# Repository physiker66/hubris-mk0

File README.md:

# hubris-mk0
homebrew computer based on 74xx chips

This work is based in large parts on Ben Eaters tutorial (see: https://eater.net). Ben's contributions are greatly appreciated.

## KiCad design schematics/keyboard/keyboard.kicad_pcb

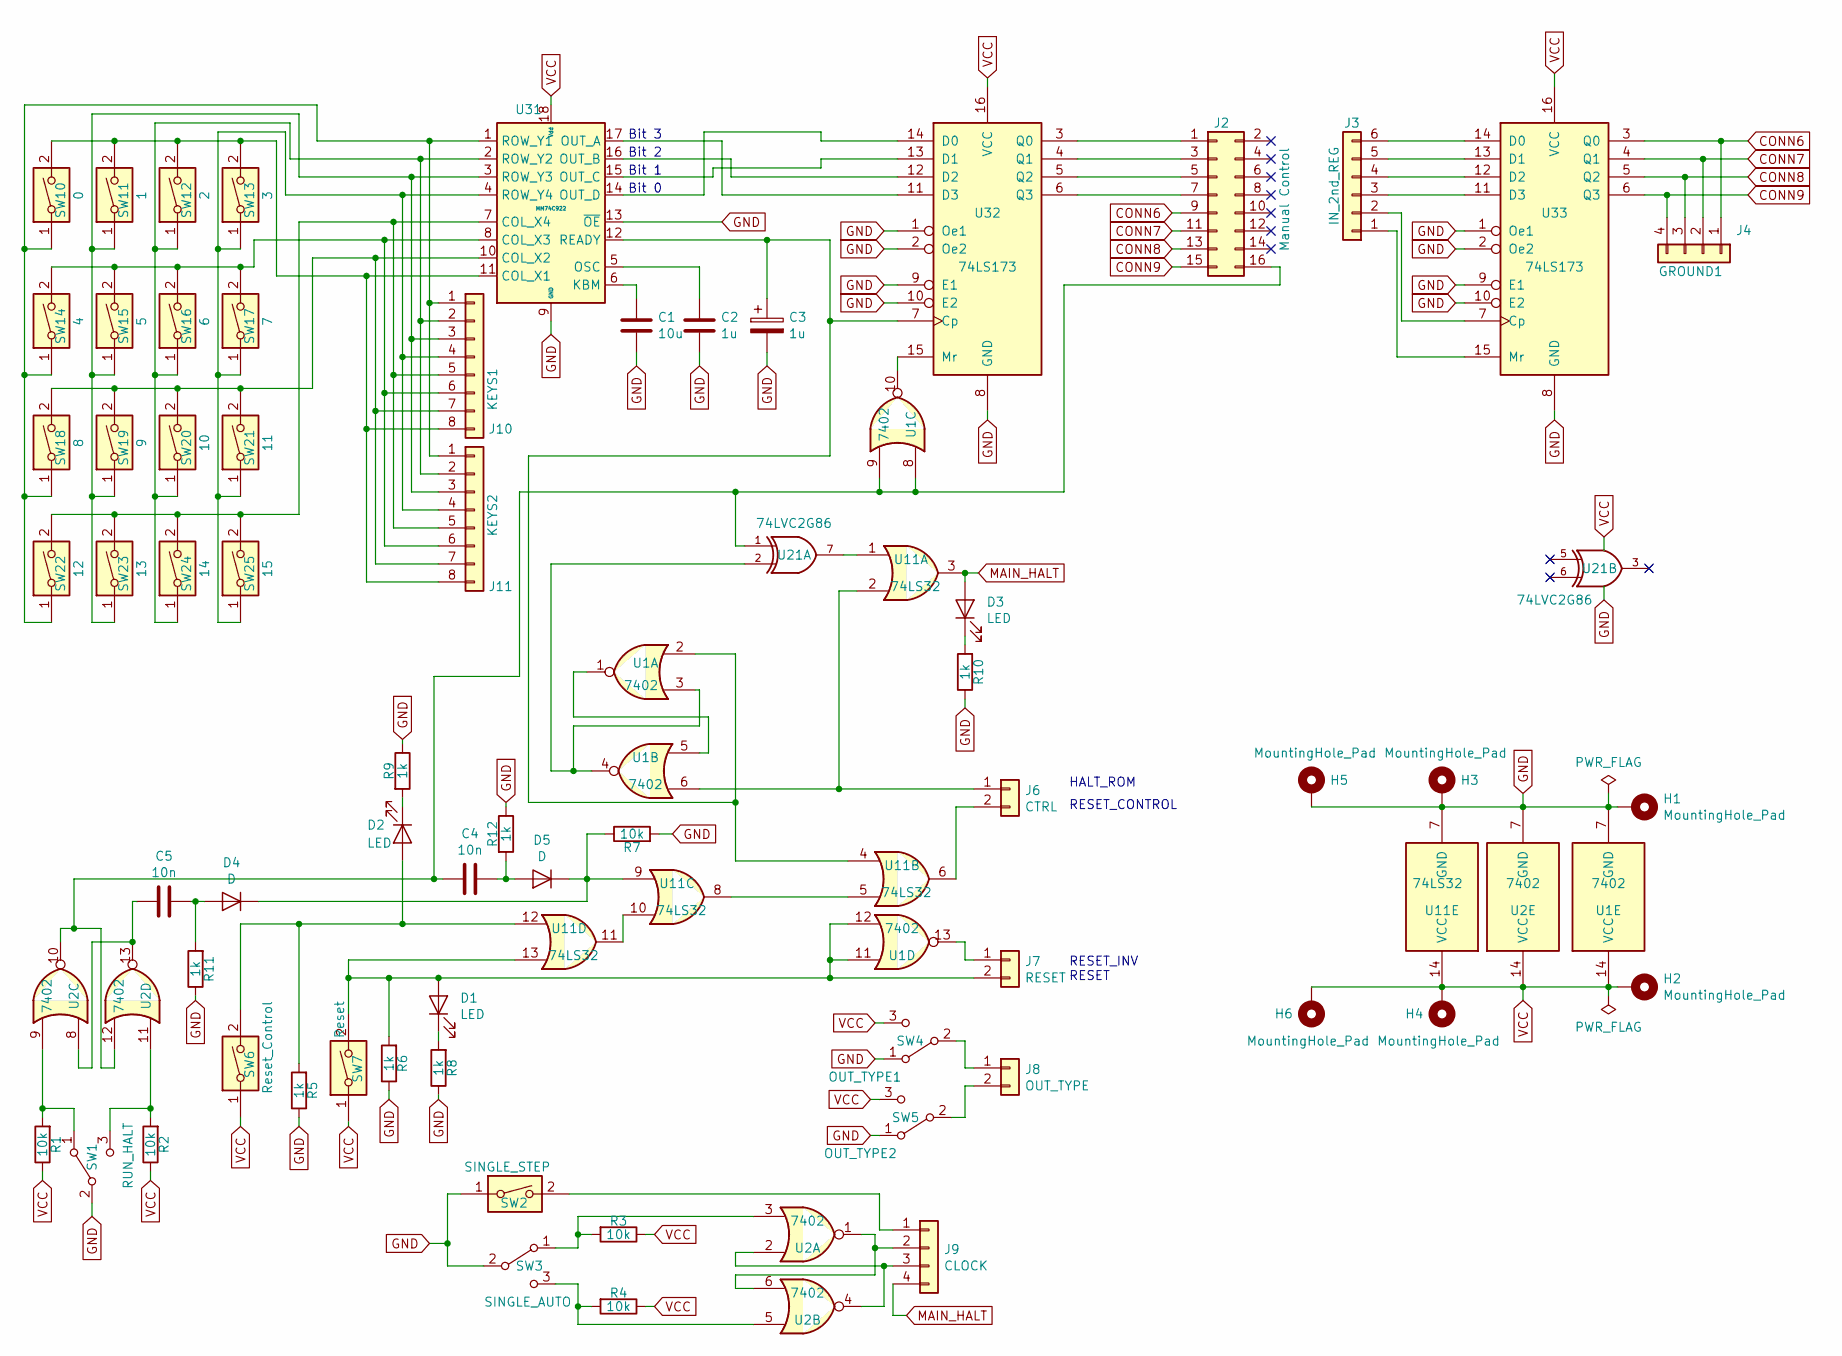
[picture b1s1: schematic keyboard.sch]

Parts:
C1: 10u; CP_Radial_D5.0mm_P2.50mm
C2: 1u; CP_Radial_D5.0mm_P2.50mm
C3: 1u; CP_Radial_D6.3mm_P2.50mm
C4, C5: 10n; C_Disc_D5.0mm_W2.5mm_P2.50mm
D1, D2, D3: LED; LED_D5.0mm
D4, D5: D; D_A-405_P7.62mm_Horizontal
H1, H2, H3, H4, H5, H6: MountingHole_Pad; MountingHole_3.5mm_Pad_Via
J2: Manual Control; PinHeader_2x08_P2.54mm_Vertical
J3: IN_2nd_REG; PinHeader_1x06_P2.54mm_Vertical
J4: GROUND1; PinHeader_1x04_P2.54mm_Vertical
J6: CTRL; PinHeader_1x02_P2.54mm_Vertical
J7: RESET; PinHeader_1x02_P2.54mm_Vertical
J8: OUT_TYPE; PinHeader_1x02_P2.54mm_Vertical
J9: CLOCK; PinHeader_1x04_P2.54mm_Vertical
J10: KEYS1; PinHeader_1x08_P2.54mm_Vertical
J11: KEYS2; PinHeader_1x08_P2.54mm_Vertical
R1, R2, R3, R4, R7: 10k; R_Axial_DIN0207_L6.3mm_D2.5mm_P7.62mm_Horizontal
R5, R6, R8, R9, R10, R11, R12: 1k; R_Axial_DIN0207_L6.3mm_D2.5mm_P7.62mm_Horizontal
SW1: RUN_HALT; SW_SPDT_1P2T
SW2: SINGLE_STEP; SW_PUSH-12mm
SW3: SINGLE_AUTO; SW_SPDT_1P2T
SW4: OUT_TYPE1; SW_Slide_1P2T
SW5: OUT_TYPE2; SW_Slide_1P2T
SW6: Reset_Control; SW_PUSH-12mm
SW7: Reset; SW_PUSH-12mm
SW10: 0; SW_PUSH-12mm
SW11: 1; SW_PUSH-12mm
SW12: 2; SW_PUSH-12mm
SW13: 3; SW_PUSH-12mm
SW14: 4; SW_PUSH-12mm
SW15: 5; SW_PUSH-12mm
SW16: 6; SW_PUSH-12mm
SW17: 7; SW_PUSH-12mm
SW18: 8; SW_PUSH-12mm
SW19: 9; SW_PUSH-12mm
SW20: 10; SW_PUSH-12mm
SW21: 11; SW_PUSH-12mm
SW22: 12; SW_PUSH-12mm
SW23: 13; SW_PUSH-12mm
SW24: 14; SW_PUSH-12mm
SW25: 15; SW_PUSH-12mm
U1, U2: 7402; DIP-14_W7.62mm
U11: 74LS32; DIP-14_W7.62mm
U21: 74LVC2G86; DIP-8_W7.62mm
U31: MM74C922; DIP-18_W7.62mm
U32, U33: 74LS173; DIP-16_W7.62mm

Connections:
CONN6: J2.9, J4.1, U33.3 (Q0)
CONN7: J2.11, J4.2, U33.4 (Q1)
CONN8: J2.13, J4.3, U33.5 (Q2)
CONN9: J2.15, J4.4, U33.6 (Q3)
GND: C1.2, C2.2, C3.2, H1.1, H3.1, H5.1, R5.1, R6.1, R7.2, R8.1, R9.1, R10.1, R11.1, R12.1, SW1.2 (B), SW2.1, SW3.2 (B), SW4.1 (A), SW5.1 (A), U1.7 (GND), U2.7 (GND), U11.7 (GND), U21.4 (GND), U31.9 (GND), U31.13 (~OE~), U32.1 (Oe1), U32.2 (Oe2), U32.8 (GND), U32.9 (E1), U32.10 (E2), U33.1 (Oe1), U33.2 (Oe2), U33.8 (GND), U33.9 (E1), U33.10 (E2)
MAIN_HALT: D3.2 (A), J9.4, U11.3
unnamed: C1.1, U31.6 (KBM)
unnamed: C2.1, U31.5 (OSC)
unnamed: C3.1, U1.2, U11.4, U31.12 (READY), U32.7 (Cp)
unnamed: C4.1, D5.2 (A), R12.2
unnamed: C4.2, J2.16, U1.8, U1.9, U2.10, U2.12, U21.1
unnamed: C5.1, D4.2 (A), R11.2
unnamed: C5.2, U2.8, U2.13
unnamed: D1.1 (K), R8.2
unnamed: D1.2 (A), J7.2, R6.2, SW7.2, U1.11, U1.12, U11.13
unnamed: D2.1 (K), R9.2
unnamed: D2.2 (A), R5.2, SW6.2, U11.12
unnamed: D3.1 (K), R10.2
unnamed: D4.1 (K), D5.1 (K), R7.1, U11.9
unnamed: J2.1, U32.3 (Q0)
unnamed: J2.3, U32.4 (Q1)
unnamed: J2.5, U32.5 (Q2)
unnamed: J2.7, U32.6 (Q3)
unnamed: J3.1, U33.15 (Mr)
unnamed: J3.2, U33.7 (Cp)
unnamed: J3.3, U33.11 (D3)
unnamed: J3.4, U33.12 (D2)
unnamed: J3.5, U33.13 (D1)
unnamed: J3.6, U33.14 (D0)
unnamed: J6.1, U1.6, U11.2
unnamed: J6.2, U11.6
unnamed: J7.1, U1.13
unnamed: J8.1, SW4.2 (B)
unnamed: J8.2, SW5.2 (B)
unnamed: J9.1, SW2.2
unnamed: J9.2, U2.1, U2.6
unnamed: J9.3, U2.2, U2.4
unnamed: J10.1, J11.1, SW10.1, SW14.1, SW18.1, SW22.1, U31.1 (ROW_Y1)
unnamed: J10.2, J11.2, SW12.1, SW16.1, SW20.1, SW24.1, U31.2 (ROW_Y2)
unnamed: J10.3, J11.3, SW11.1, SW15.1, SW19.1, SW23.1, U31.3 (ROW_Y3)
unnamed: J10.4, J11.4, SW13.1, SW17.1, SW21.1, SW25.1, U31.4 (ROW_Y4)
unnamed: J10.5, J11.5, SW22.2, SW23.2, SW24.2, SW25.2, U31.7 (COL_X4)
unnamed: J10.6, J11.6, SW14.2, SW15.2, SW16.2, SW17.2, U31.8 (COL_X3)
unnamed: J10.7, J11.7, SW18.2, SW19.2, SW20.2, SW21.2, U31.10 (COL_X2)
unnamed: J10.8, J11.8, SW10.2, SW11.2, SW12.2, SW13.2, U31.11 (COL_X1)
unnamed: R1.2, SW1.1 (A), U2.9
unnamed: R2.2, SW1.3 (C), U2.11
unnamed: R3.2, SW3.1 (A), U2.3
unnamed: R4.2, SW3.3 (C), U2.5
unnamed: U1.1, U1.5
unnamed: U1.3, U1.4, U21.2
unnamed: U1.10, U32.15 (Mr)
unnamed: U11.1, U21.7
unnamed: U11.5, U11.8
unnamed: U11.10, U11.11
unnamed: U31.14 (OUT_D), U32.14 (D0)
unnamed: U31.15 (OUT_C), U32.13 (D1)
unnamed: U31.16 (OUT_B), U32.12 (D2)
unnamed: U31.17 (OUT_A), U32.11 (D3)
VCC: H2.1, H4.1, H6.1, R1.1, R2.1, R3.1, R4.1, SW4.3 (C), SW5.3 (C), SW6.1, SW7.1, U1.14 (VCC), U2.14 (VCC), U11.14 (VCC), U21.8 (VCC), U31.18 (Vdd), U32.16 (VCC), U33.16 (VCC)

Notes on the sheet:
RESET_INV RESET
HALT_ROM
RESET_CONTROL
Bit 0
Bit 1
Bit 2
Bit 3

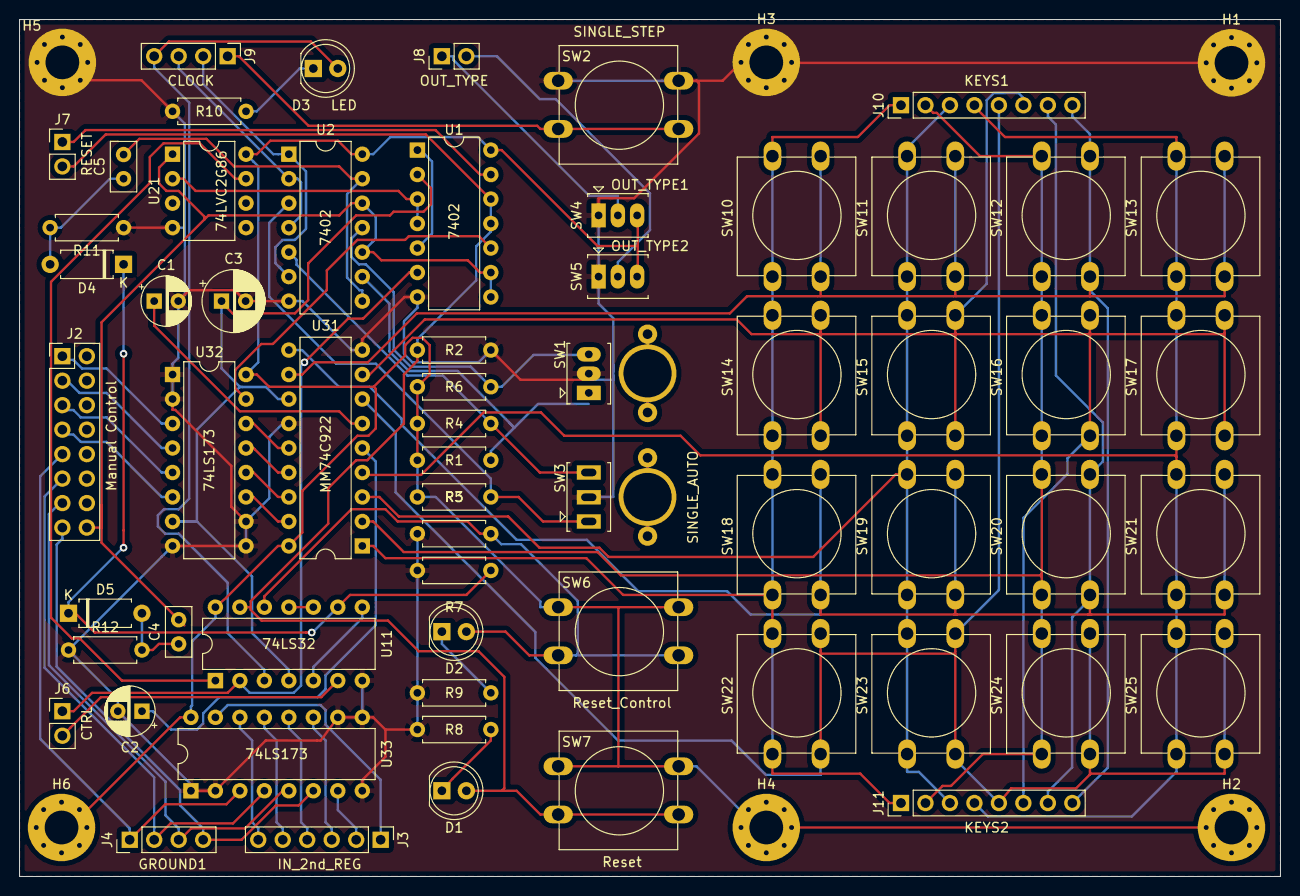
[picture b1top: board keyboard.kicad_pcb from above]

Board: 2 copper layers, 130.8 x 88.9 mm, 67 parts (0 on the bottom side), 60 nets.

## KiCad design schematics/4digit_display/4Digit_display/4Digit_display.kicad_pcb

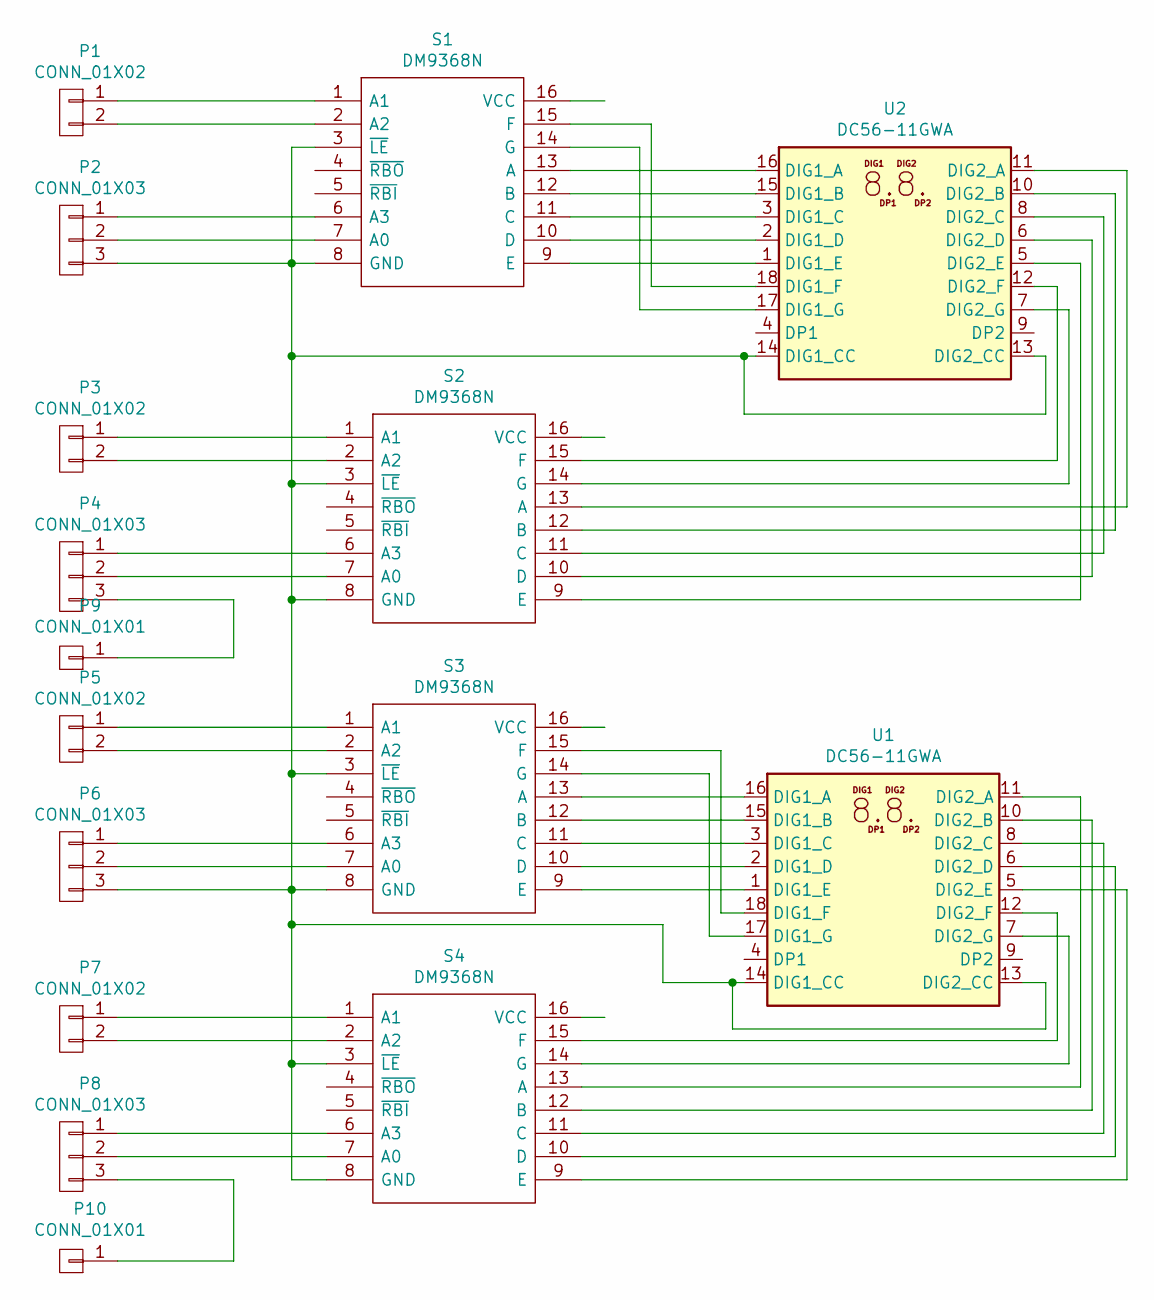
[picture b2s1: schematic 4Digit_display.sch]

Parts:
P1: CONN_01X02; PinSocket_1x02_P2.54mm_Vertical
P2, P4, P6, P8: CONN_01X03; PinHeader_1x03_P2.54mm_Vertical
P3, P5, P7: CONN_01X02; PinHeader_1x02_P2.54mm_Vertical
P9, P10: CONN_01X01; PinHeader_1x01_P2.54mm_Vertical
S1, S2, S3, S4: DM9368N; DIP-16_W7.62mm; Manufacturer_Part_Number DM9368N; Mouser Part Number 512-DM9368N
U1, U2: DC56-11GWA; DA56-11CGKWA

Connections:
unnamed: P1.1, S1.1 (A1)
unnamed: P1.2, S1.2 (A2)
unnamed: P2.1, S1.6 (A3)
unnamed: P2.2, S1.7 (A0)
unnamed: P2.3, P6.3, S1.3 (~LE), S1.8 (GND), S2.3 (~LE), S2.8 (GND), S3.3 (~LE), S3.8 (GND), S4.3 (~LE), S4.8 (GND), U1.13 (DIG2_CC), U1.14 (DIG1_CC), U2.13 (DIG2_CC), U2.14 (DIG1_CC)
unnamed: P3.1, S2.1 (A1)
unnamed: P3.2, S2.2 (A2)
unnamed: P4.1, S2.6 (A3)
unnamed: P4.2, S2.7 (A0)
unnamed: P4.3, P9.1
unnamed: P5.1, S3.1 (A1)
unnamed: P5.2, S3.2 (A2)
unnamed: P6.1, S3.6 (A3)
unnamed: P6.2, S3.7 (A0)
unnamed: P7.1, S4.1 (A1)
unnamed: P7.2, S4.2 (A2)
unnamed: P8.1, S4.6 (A3)
unnamed: P8.2, S4.7 (A0)
unnamed: P8.3, P10.1
unnamed: S1.9 (E), U2.1 (DIG1_E)
unnamed: S1.10 (D), U2.2 (DIG1_D)
unnamed: S1.11 (C), U2.3 (DIG1_C)
unnamed: S1.12 (B), U2.15 (DIG1_B)
unnamed: S1.13 (A), U2.16 (DIG1_A)
unnamed: S1.14 (G), U2.17 (DIG1_G)
unnamed: S1.15 (F), U2.18 (DIG1_F)
unnamed: S2.9 (E), U2.5 (DIG2_E)
unnamed: S2.10 (D), U2.6 (DIG2_D)
unnamed: S2.11 (C), U2.8 (DIG2_C)
unnamed: S2.12 (B), U2.10 (DIG2_B)
unnamed: S2.13 (A), U2.11 (DIG2_A)
unnamed: S2.14 (G), U2.7 (DIG2_G)
unnamed: S2.15 (F), U2.12 (DIG2_F)
unnamed: S3.9 (E), U1.1 (DIG1_E)
unnamed: S3.10 (D), U1.2 (DIG1_D)
unnamed: S3.11 (C), U1.3 (DIG1_C)
unnamed: S3.12 (B), U1.15 (DIG1_B)
unnamed: S3.13 (A), U1.16 (DIG1_A)
unnamed: S3.14 (G), U1.17 (DIG1_G)
unnamed: S3.15 (F), U1.18 (DIG1_F)
unnamed: S4.9 (E), U1.5 (DIG2_E)
unnamed: S4.10 (D), U1.6 (DIG2_D)
unnamed: S4.11 (C), U1.8 (DIG2_C)
unnamed: S4.12 (B), U1.10 (DIG2_B)
unnamed: S4.13 (A), U1.11 (DIG2_A)
unnamed: S4.14 (G), U1.7 (DIG2_G)
unnamed: S4.15 (F), U1.12 (DIG2_F)

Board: 2 copper layers, 16 parts (0 on the bottom side), 47 nets, no tracks yet.

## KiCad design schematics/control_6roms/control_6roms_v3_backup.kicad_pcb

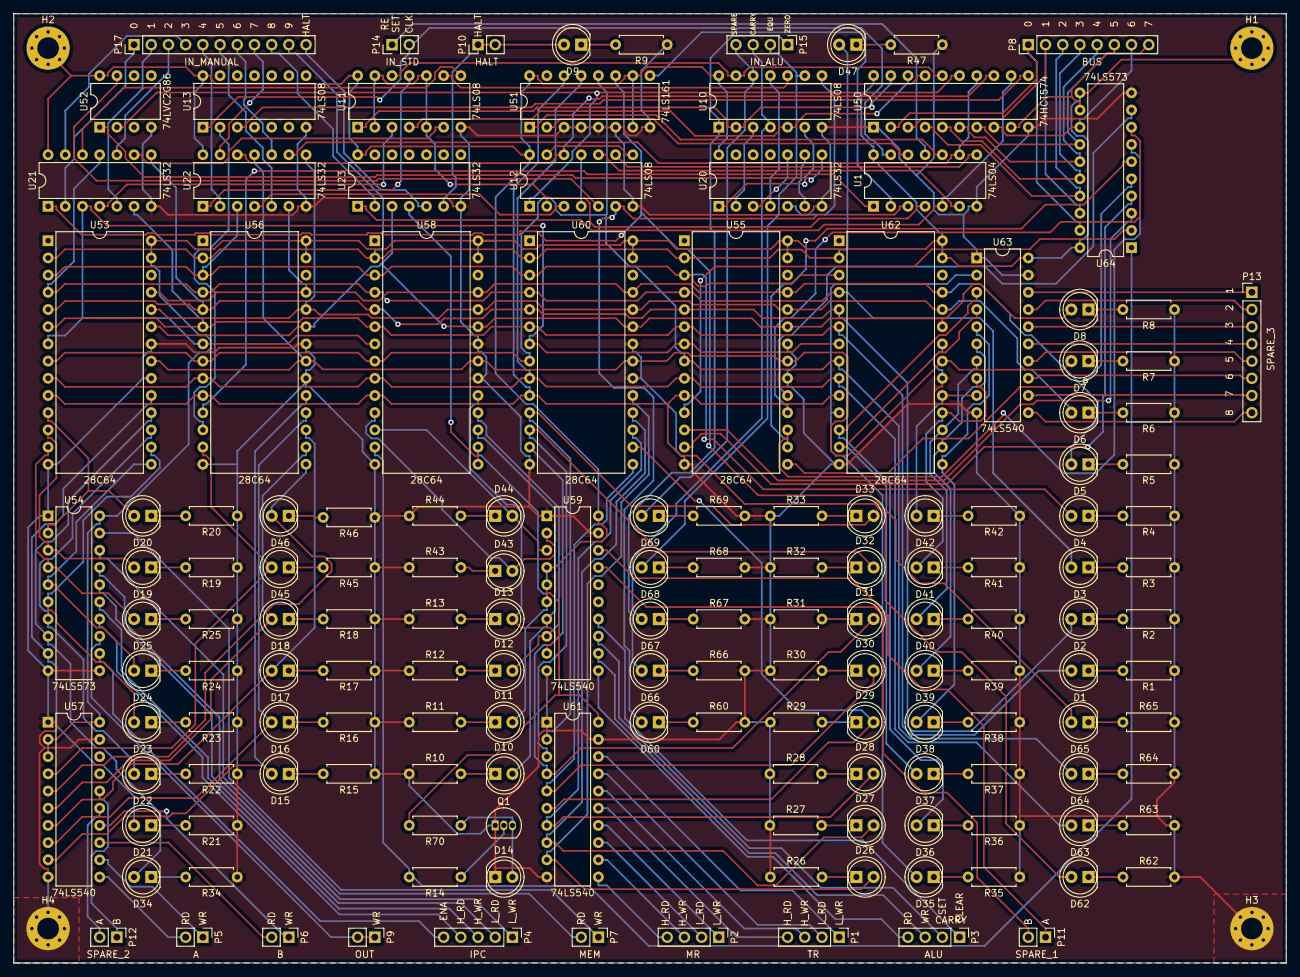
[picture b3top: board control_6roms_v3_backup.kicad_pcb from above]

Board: 2 copper layers, 188.0 x 140.2 mm, 158 parts (0 on the bottom side), 213 nets.

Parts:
D1: ADDR_04; LED_D5.0mm
D2: ADDR_05; LED_D5.0mm
D3: ADDR_06; LED_D5.0mm
D4: ADDR_07; LED_D5.0mm
D5: ADDR_08; LED_D5.0mm
D6: ADDR_09; LED_D5.0mm
D7: ADDR_10; LED_D5.0mm
D8: ADDR_11; LED_D5.0mm
D9: HALT; LED_D5.0mm
D10: SET_CARRY; LED_D5.0mm
D11: CLEAR_CARRY; LED_D5.0mm
D12: ALU_WR; LED_D5.0mm
D13: ALU_RD; LED_D5.0mm
D14: BUS_WR; LED_D5.0mm
D15: A_RD; LED_D5.0mm
D16: A_WR; LED_D5.0mm
D17: B_RD; LED_D5.0mm
D18: B_WR; LED_D5.0mm
D19: MEM_RD; LED_D5.0mm
D20: MEM_WR; LED_D5.0mm
D21: IPC_INC; LED_D5.0mm
D22: IPC_RD_HIGH; LED_D5.0mm
D23: IPC_WR_HIGH; LED_D5.0mm
D24: IPC_RD_LOW; LED_D5.0mm
D25: IPC_WR_LOW; LED_D5.0mm
D26: MR_RD_HIGH; LED_D5.0mm
D27: MR_WR_HIGH; LED_D5.0mm
D28: MR_READ_LOW; LED_D5.0mm
D29: MR_WR_LOW; LED_D5.0mm
D30: TR_RD_HIGH; LED_D5.0mm
D31: TR_WR_HIGH; LED_D5.0mm
D32: TR_RD_LOW; LED_D5.0mm
D33: TR_WR_LOW; LED_D5.0mm
D34: OUT_WR; LED_D5.0mm
D35: SPARE_1; LED_D5.0mm
D36: SPARE_2; LED_D5.0mm
D37: SPARE_3; LED_D5.0mm
D38: SPARE_4; LED_D5.0mm
D39: SPARE_5; LED_D5.0mm
D40: SPARE_6; LED_D5.0mm
D41: SPARE_7; LED_D5.0mm
D42: SPARE_8; LED_D5.0mm
D43: SPARE_A; LED_D5.0mm
D44: SPARE_B; LED_D5.0mm
D45: SPARE_C; LED_D5.0mm
D46: SPARE_D; LED_D5.0mm
D47: MANUAL; LED_D5.0mm
D60: JMP; LED_D5.0mm
D62: STEP0; LED_D5.0mm
D63: STEP1; LED_D5.0mm
D64: STEP2; LED_D5.0mm
D65: STEP3; LED_D5.0mm
D66: ZERO; LED_D5.0mm
D67: CARRY; LED_D5.0mm
D68: EQUAL; LED_D5.0mm
D69: SPARE; LED_D5.0mm
H1: TOP_RIGHT_VCC; MountingHole_3.2mm_M3_Pad_Via
H2: TOP_LEFT_VCC; MountingHole_3.2mm_M3_Pad_Via
H3: BOTTOM_RIGHT_GND; MountingHole_3.2mm_M3_Pad_Via
H4: BOTTOM_LEFT_GND; MountingHole_3.2mm_M3_Pad_Via
P1: TR; PinHeader_1x04_P2.54mm_Vertical
P2: MR; PinHeader_1x04_P2.54mm_Vertical
P3: ALU; PinHeader_1x04_P2.54mm_Vertical
P4: IPC; PinHeader_1x05_P2.54mm_Vertical
P5: A; PinHeader_1x02_P2.54mm_Vertical
P6: B; PinHeader_1x02_P2.54mm_Vertical
P7: MEM; PinHeader_1x02_P2.54mm_Vertical
P8: BUS; PinHeader_1x08_P2.54mm_Vertical
P9: OUT; PinHeader_1x02_P2.54mm_Vertical
P10: HALT; PinHeader_1x02_P2.54mm_Vertical
P11: SPARE_1; PinHeader_1x02_P2.54mm_Vertical
P12: SPARE_2; PinHeader_1x02_P2.54mm_Vertical
P13: SPARE_3; PinHeader_1x08_P2.54mm_Vertical
P14: IN_STD; PinHeader_1x02_P2.54mm_Vertical
P15: IN_ALU; PinHeader_1x04_P2.54mm_Vertical
P17: IN_MANUAL; PinHeader_1x11_P2.54mm_Vertical
Q1: 2N3904; TO-92_Inline
R1, R2, R3, R4, R5, R6, R7, R8, R9, R10, R11, R12, R13, R14, R15, R16, R17, R18, R19, R20, R21, R22, R23, R24, R25, R26, R27, R28, R29, R30, R31, R32, R33, R34, R35, R36, R37, R38, R39, R40, R41, R42, R43, R44, R45, R46, R47, R60, R62, R63, R64, R65, R66, R67, R68, R69, R70: 10k; R_Axial_DIN0207_L6.3mm_D2.5mm_P7.62mm_Horizontal
U1: 74LS04; DIP-14_W7.62mm
U10, U11, U12, U13: 74LS08; DIP-14_W7.62mm
U20, U21, U22, U23: 74LS32; DIP-14_W7.62mm
U50: 74HCT574; DIP-20_W7.62mm
U51: 74LS161; DIP-16_W7.62mm
U52: 74LVC2G86; DIP-8_W7.62mm
U53, U55, U56, U58, U60, U62: 28C64; DIP-28_W15.24mm
U54, U64: 74LS573; DIP-20_W7.62mm
U57, U59, U61, U63: 74LS540; DIP-20_W7.62mm

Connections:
ADR_00: D62.2, U51.14, U53.10, U55.10, U56.10, U58.10, U60.10, U62.10
ADR_01: D63.2, U51.13, U53.9, U55.9, U56.9, U58.9, U60.9, U62.9
ADR_02: D64.2, U51.12, U53.8, U55.8, U56.8, U58.8, U60.8, U62.8
ADR_03: U21.3, U53.7, U55.7, U56.7, U58.7, U60.7, U62.7
ADR_04: D1.2, U21.6, U53.6, U55.6, U56.6, U58.6, U60.6, U62.6
ADR_05: D2.2, U21.8, U53.5, U55.5, U56.5, U58.5, U60.5, U62.5
ADR_06: D3.2, U21.11, U53.4, U55.4, U56.4, U58.4, U60.4, U62.4
ADR_07: D4.2, U22.3, U53.3, U55.3, U56.3, U58.3, U60.3, U62.3
ADR_08: D5.2, U22.6, U53.25, U55.25, U56.25, U58.25, U60.25, U62.25
ADR_09: D6.2, U22.8, U53.24, U55.24, U56.24, U58.24, U60.24, U62.24
ADR_10: D7.2, U22.11, U53.21, U55.21, U56.21, U58.21, U60.21, U62.21
ADR_11: D8.2, U23.3, U53.23, U55.23, U56.23, U58.23, U60.23, U62.23
ADR_12: D47.2, P17.10, U53.2, U55.2, U56.2, U58.2, U60.2, U62.2
BUS_WR: R14.2, U58.13, U64.1
CLK: P14.2, U1.13, U13.1
END_INSTRUCTION: U1.1, U56.11
EQUAL: D68.2, P15.2, U10.9
GND: D14.1, H3.1, H4.1, Q1.1, R1.1, R2.1, R3.1, R4.1, R5.1, R6.1, R7.1, R8.1, R9.1, R10.1, R11.1, R12.1, R13.1, R15.1, R16.1, R17.1, R18.1, R19.1, R20.1, R21.1, R22.1, R23.1, R24.1, R25.1, R26.1, R27.1, R28.1, R29.1, R30.1, R31.1, R32.1, R33.1, R34.1, R35.1, R36.1, R37.1, R38.1, R39.1, R40.1, R41.1, R42.1, R43.1, R44.1, R45.1, R46.1, R47.1, R60.2, R62.2, R63.2, R64.2, R65.2, R66.2, R67.2, R68.2, R69.2, U1.7, U10.7, U11.7, U12.7, U13.7, U20.7, U21.7, U22.7, U23.7, U50.1, U50.10, U51.3, U51.4, U51.5, U51.6, U51.8, U52.4, U53.14, U53.20, U53.22, U54.1, U54.10, U54.11, U55.14, U55.20, U55.22, U56.14, U56.20, U56.22, U57.1, U57.10, U57.19, U58.14, U58.20, U58.22, U59.1, U59.10, U59.19, U60.14, U60.20, U60.22, U61.1, U61.10, U61.19, U62.14, U62.20, U62.22, U63.1, U63.10, U63.19, U64.10
IN_CARRY: D67.2, P15.3, U10.4
IN_SPARE: D69.2, P15.4, U10.12
IN_ZERO: D66.2, P15.1, U10.1
MANUAL_0: P17.1, U21.2
MANUAL_1: P17.2, U21.5
MANUAL_2: P17.3, U21.10
MANUAL_3: P17.4, U21.13
MANUAL_4: P17.5, U22.2
MANUAL_5: P17.6, U22.5
MANUAL_6: P17.7, U22.10
MANUAL_7: P17.8, U22.13
MANUAL_8: P17.9, U23.2
MANUAL_HALT: P17.11, U23.5
unnamed: D1.1, R1.2
unnamed: D2.1, R2.2
unnamed: D3.1, R3.2
unnamed: D4.1, R4.2
unnamed: D5.1, R5.2
unnamed: D6.1, R6.2
unnamed: D7.1, R7.2
unnamed: D8.1, R8.2
unnamed: D9.1, R9.2
unnamed: D10.1, R10.2
unnamed: D11.1, R11.2
unnamed: D12.1, R12.2
unnamed: D13.1, R13.2
unnamed: D14.2, Q1.3, R70.1
unnamed: D15.1, R15.2
unnamed: D16.1, R16.2
unnamed: D17.1, R17.2
unnamed: D18.1, R18.2
unnamed: D19.1, R19.2
unnamed: D20.1, R20.2
unnamed: D21.1, R21.2
unnamed: D22.1, R22.2
unnamed: D23.1, R23.2
unnamed: D24.1, R24.2
unnamed: D25.1, R25.2
unnamed: D26.1, R26.2
unnamed: D27.1, R27.2
unnamed: D28.1, R28.2
unnamed: D29.1, R29.2
unnamed: D30.1, R30.2
unnamed: D31.1, R31.2
unnamed: D32.1, R32.2
unnamed: D33.1, R33.2
unnamed: D34.1, R34.2
unnamed: D35.1, R35.2
unnamed: D36.1, R36.2
unnamed: D37.1, R37.2
unnamed: D38.1, R38.2
unnamed: D39.1, R39.2
unnamed: D40.1, R40.2
unnamed: D41.1, R41.2
unnamed: D42.1, R42.2
unnamed: D43.1, R43.2
unnamed: D44.1, R44.2
unnamed: D45.1, R45.2
unnamed: D46.1, R46.2
unnamed: D47.1, R47.2
unnamed: D60.1, R60.1
unnamed: U1.4, U11.2, U11.5, U11.10, U11.13, U12.2
unnamed: D62.1, R62.1
unnamed: D63.1, R63.1
unnamed: D64.1, R64.1
unnamed: D65.1, R65.1
unnamed: D65.2, U21.1, U51.11
unnamed: D66.1, R66.1
unnamed: D67.1, R67.1
unnamed: D68.1, R68.1
unnamed: D69.1, R69.1
unnamed: Q1.2, R14.1
unnamed: U1.2, U51.9
unnamed: D60.2, U1.3, U12.6
unnamed: U1.5, U23.1, U50.12
unnamed: U1.6, U12.10
unnamed: U1.8, U12.9
unnamed: U1.9, U22.9, U50.14
unnamed: U1.10, U51.1
unnamed: U1.12, U51.2
unnamed: U10.2, U11.1, U50.19
unnamed: U10.3, U20.2
unnamed: U10.5, U11.4, U50.18
unnamed: U10.6, U20.1
unnamed: U10.8, U20.5
unnamed: U10.10, U11.9, U50.17
unnamed: U10.11, U20.4
unnamed: U10.13, U11.12, U50.16
unnamed: U11.3, U21.4
unnamed: U11.6, U21.9
unnamed: U11.8, U21.12
unnamed: U11.11, U22.1
unnamed: U12.1, U50.15, U52.2
unnamed: U12.3, U22.4
unnamed: U12.5, U52.7
unnamed: U12.4, U12.11
unnamed: U12.12, U22.12, U50.13
unnamed: U12.8, U12.13
unnamed: U13.3, U50.11
unnamed: U20.6, U20.9
unnamed: U20.8, U52.1
unnamed: U20.3, U20.10
unnamed: U55.11, U64.2
unnamed: U55.12, U64.3
unnamed: U55.13, U64.4
unnamed: U55.15, U64.5
unnamed: U55.16, U64.6
unnamed: U55.17, U64.7
unnamed: U55.18, U64.8
unnamed: U55.19, U64.9
OUT_ALU_RD: P3.4, U59.11
OUT_ALU_WR: P3.3, U59.12
OUT_A_RD: P5.2, U57.11
OUT_A_WR: P5.1, U57.12
OUT_BUS_0: P8.1, U50.2, U64.19
OUT_BUS_1: P8.2, U50.3, U64.18
OUT_BUS_2: P8.3, U50.4, U64.17
OUT_BUS_3: P8.4, U50.5, U64.16
OUT_BUS_4: P8.5, U50.6, U64.15
OUT_BUS_5: P8.6, U50.7, U64.14
OUT_BUS_6: P8.7, U50.8, U64.13
OUT_BUS_7: P8.8, U50.9, U64.12
OUT_B_RD: P6.2, U57.13
OUT_B_WR: P6.1, U57.14
OUT_CARRY_CLEAR: P3.1, U59.14
OUT_CARRY_SET: P3.2, U59.13
OUT_HALT: D9.2, P10.1, P10.2, U23.6
OUT_IPC_HIGH_RD: P4.4, U54.14
OUT_IPC_HIGH_WR: P4.3, U54.15
OUT_IPC_INC: P4.5, U54.12
OUT_IPC_LOW_RD: P4.2, U54.16
OUT_IPC_LOW_WR: P4.1, U54.17
OUT_MEM_RD: P7.2, U54.18
OUT_MEM_WR: P7.1, U54.19
OUT_MR_HIGH_RD: P2.4, U61.11
OUT_MR_HIGH_WR: P2.3, U61.12
OUT_MR_LOW_RD: P2.2, U61.13
OUT_MR_LOW_WR: P2.1, U61.14
OUT_OUT_WR: P9.1, P9.2, U54.13
OUT_SPARE_1: P13.1, U63.18
OUT_SPARE_2: P13.2, U63.17
OUT_SPARE_3: P13.3, U63.16
OUT_SPARE_4: P13.4, U63.15
OUT_SPARE_5: P13.5, U63.14
OUT_SPARE_6: P13.6, U63.13
OUT_SPARE_7: P13.7, U63.12
OUT_SPARE_8: P13.8, U63.11
OUT_SPARE_A: P11.1, U59.18
OUT_SPARE_B: P11.2, U59.17
OUT_SPARE_C: P12.1, U57.16
OUT_SPARE_D: P12.2, U57.15
OUT_TR_HIGH_RD: P1.4, U61.15
OUT_TR_HIGH_WR: P1.3, U61.16
OUT_TR_LOW_RD: P1.2, U61.17
OUT_TR_LOW_WR: P1.1, U61.18
PROG_WR: U13.2, U56.12
RESET: P14.1, U1.11
ROM_ALU_RD: D13.2, U58.19, U59.9
ROM_ALU_WR: D12.2, U58.18, U59.8
ROM_A_RD: D15.2, U56.19, U57.9
ROM_A_WR: D16.2, U56.18, U57.8
ROM_B_RD: D17.2, U56.17, U57.7
ROM_B_WR: D18.2, U56.16, U57.6
ROM_CARRY_CLEAR: D11.2, U58.16, U59.6
ROM_CARRY_SET: D10.2, U58.17, U59.7
ROM_HALT: U23.4, U58.15
ROM_IPC_HIGH_RD: D22.2, U53.17, U54.7
ROM_IPC_HIGH_WR: D23.2, U53.16, U54.6
ROM_IPC_INC: D21.2, U53.19, U54.9
ROM_IPC_LOW_RD: D24.2, U53.15, U54.5
ROM_IPC_LOW_WR: D25.2, U53.13, U54.4
ROM_MEM_RD: D19.2, U53.12, U54.3
ROM_MEM_WR: D20.2, U53.11, U54.2
ROM_MR_HIGH_RD: D26.2, U60.19, U61.9
ROM_MR_HIGH_WR: D27.2, U60.18, U61.8
ROM_MR_LOW_RD: D28.2, U60.17, U61.7
ROM_MR_LOW_WR: D29.2, U60.16, U61.6
ROM_OUT_WR: D34.2, U53.18, U54.8
ROM_SPARE_C: D45.2, U56.13, U57.4
ROM_SPARE_D: D46.2, U56.15, U57.5
ROM_TR_HIGH_RD: D30.2, U60.15, U61.5
ROM_TR_HIGH_WR: D31.2, U60.13, U61.4
ROM_TR_LOW_RD: D32.2, U60.12, U61.3
ROM_TR_LOW_WR: D33.2, U60.11, U61.2
SPARE_1: D35.2, U62.11, U63.2
SPARE_2: D36.2, U62.12, U63.3
SPARE_3: D37.2, U62.13, U63.4
SPARE_4: D38.2, U62.15, U63.5
SPARE_5: D39.2, U62.16, U63.6
SPARE_6: D40.2, U62.17, U63.7
SPARE_7: D41.2, U62.18, U63.8
SPARE_8: D42.2, U62.19, U63.9
SPARE_A: D43.2, U58.11, U59.2
SPARE_B: D44.2, U58.12, U59.3
VCC: H1.1, H2.1, R70.2, U1.14, U10.14, U11.14, U12.14, U13.14, U20.14, U21.14, U22.14, U23.14, U50.20, U51.7, U51.10, U51.16, U52.8, U53.27, U53.28, U54.20, U55.27, U55.28, U56.27, U56.28, U57.2, U57.3, U57.20, U58.27, U58.28, U59.4, U59.5, U59.20, U60.27, U60.28, U61.20, U62.27, U62.28, U63.20, U64.11, U64.20

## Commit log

2020-07-15 Add files via upload
    First version of the control board. The basic idea was to use only a single ROM. Turns out it's possible by sorting the commands in a compact way, and for all move commands have SRC and Target addres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
